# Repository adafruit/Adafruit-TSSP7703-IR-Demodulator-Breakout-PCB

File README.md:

## Adafruit TSSP77038 38KHz Infrared IR Demodulator Breakout - STEMMA JST PH 2mm PCB

<a href="http://www.adafruit.com/products/5940"><br/>
Click here to purchase one from the Adafruit shop</a>

PCB files for the Adafruit TSSP77038 38KHz Infrared IR Demodulator Breakout - STEMMA JST PH 2mm. 

Format is EagleCAD schematic and board layout
* https://www.adafruit.com/product/5940

### Description

While designing our IR decoding breakout we noticed the TSSP series of chips from Vishay, these are simpler than more 'remote control' receivers in that they don't do any filtering on the codes received: you really just get the demodulated-from-38KHz-signal output.

According to Vishay, they're designed for "Reflective Sensing, Light Barriers, and Fast Proximity Applications". These sensors could be interesting for use when you want a less-'intelligent' IR decoder, or for proximity projects where you don't want to go all-out for a VCNL I2C sensor. These are good for creating break-beams where the IR light is modulated rather than just solid on, because you won't be affected by other IR signals or ambient light changes.

This board will work nicely for a variety of IR detecting projects, and with mounting holes and a cable, a lot easier to mount in enclosures and on devices. Using a 2mm pitch STEMMA JST PH cable with headers or alligator clips on the end, you can easily wire this board without any soldering.

Note that this board is specifically for proximity sensing or break-beam projects, while it can receive 38KHz IR remote control signals - there isn't a filter system so you'll get a lot of spurious signals.

Each STEMMA board is a fully assembled and tested PCB but no cable. No soldering is required to use it, but you will need to pick up a 2mm pitch, 3-pin STEMMA JST PH cable. Alternatively, if you do want to solder, there's a 0.1" spaced header for power/ground/signal.

### License

Adafruit invests time and resources providing this open source design, please support Adafruit and open-source hardware by purchasing products from [Adafruit](https://www.adafruit.com)!

Designed by Limor Fried/Ladyada for Adafruit Industries.

Creative Commons Attribution/Share-Alike, all text above must be included in any redistribution. 
See license.txt for additional details.

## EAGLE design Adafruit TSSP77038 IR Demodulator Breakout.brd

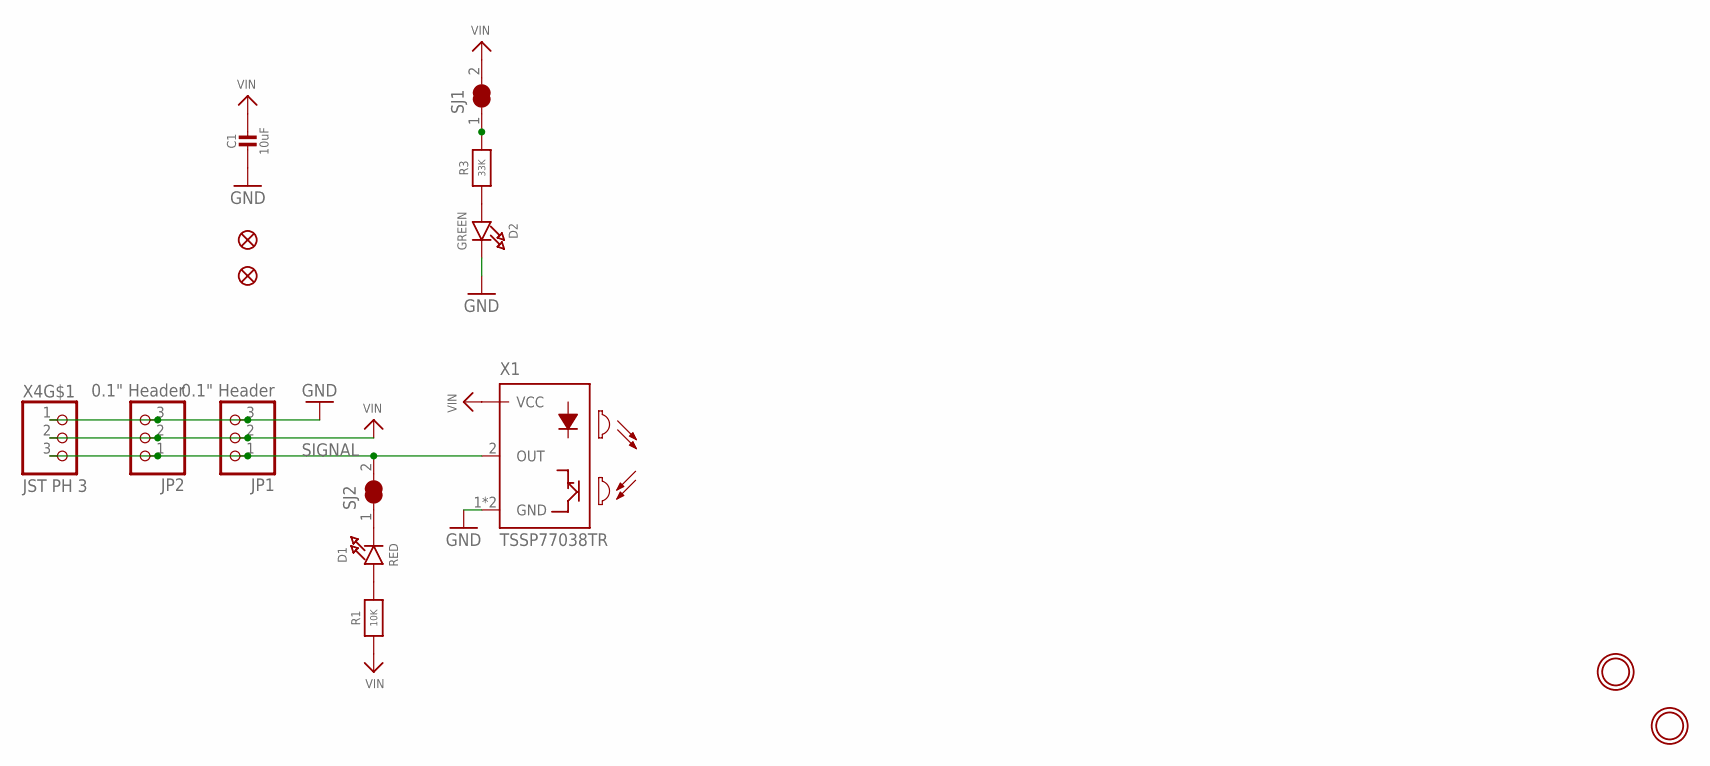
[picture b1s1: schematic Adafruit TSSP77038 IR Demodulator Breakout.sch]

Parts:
C1: 10uF; 0805-NO
D1: RED; CHIPLED_0603_NOOUTLINE
D2: GREEN; CHIPLED_0603_NOOUTLINE
FID2, FID3: FIDUCIAL_1MM
JP1: 0.1" Header; 1X03_OVAL
JP2: 0.1" Header; 1X03_ROUND_76
R1: 10K; 0603-NO
R3: 33K; 0603-NO
SJ1, SJ2: SOLDERJUMPER_CLOSED; SOLDERJUMPER_CLOSEDWIRE
U$1, U$8: MOUNTINGHOLE2.5; MOUNTINGHOLE_2.5_PLATED
X1: TSSP77038TR; VEML7700
X4: JST PH 3; JSTPH3

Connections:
GND: C1.2, D2.C, JP1.3, JP2.3, X1.1 (GND), X1.4 (GND), X4.1
unnamed: R3.2, SJ1.1
unnamed: D1.C, SJ2.1
unnamed: D1.A, R1.2
unnamed: D2.A, R3.1
SIGNAL: JP1.1, JP2.1, SJ2.2, X1.2 (OUT), X4.3
VIN: C1.1, JP1.2, JP2.2, R1.1, SJ1.2, X1.3 (VCC), X4.2

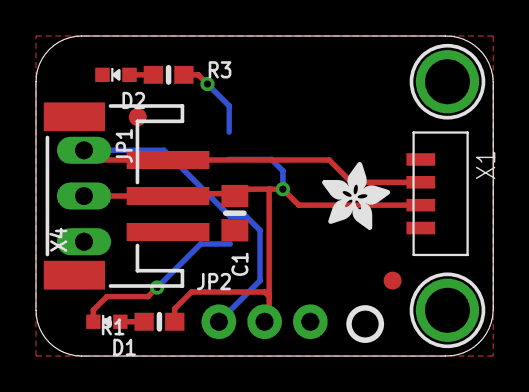
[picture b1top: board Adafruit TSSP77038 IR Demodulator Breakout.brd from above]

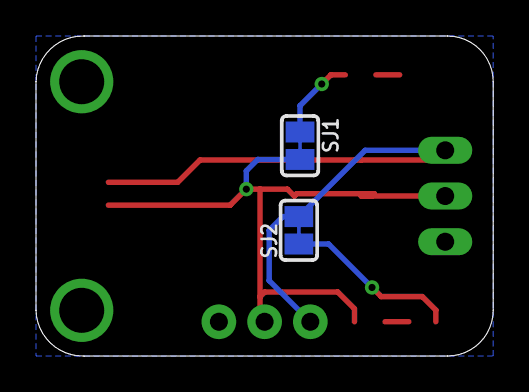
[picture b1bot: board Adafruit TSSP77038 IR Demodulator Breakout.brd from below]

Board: 2 copper layers, 25.4 x 17.8 mm, 33 parts (12 on the bottom side), 7 nets.

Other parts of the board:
PLABEL0: PLABEL0
PLABEL1: PLABEL1
PLABEL5: PLABEL5
PLABEL6: PLABEL6
PLABEL8: PLABEL8
PLABEL9: PLABEL9
PLABEL10: PLABEL10
PLABEL13: PLABEL13
PLABEL14: PLABEL14
PLABEL15: PLABEL15
PLABEL16: PLABEL16
PLABEL17: PLABEL17
PLABEL18: PLABEL18
PLABEL19: PLABEL19
PLABEL20: PLABEL20
PLABEL21: PLABEL21
U$5: PCBFEAT-REV-040
U$10: ADAFRUIT_3.5MM

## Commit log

2024-04-18 cookiecutter

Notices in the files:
parts and their libraries:
microbuilder: This work is placed in the public domain, and may be freely used for commercial and non-commercial work with the following conditions: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
